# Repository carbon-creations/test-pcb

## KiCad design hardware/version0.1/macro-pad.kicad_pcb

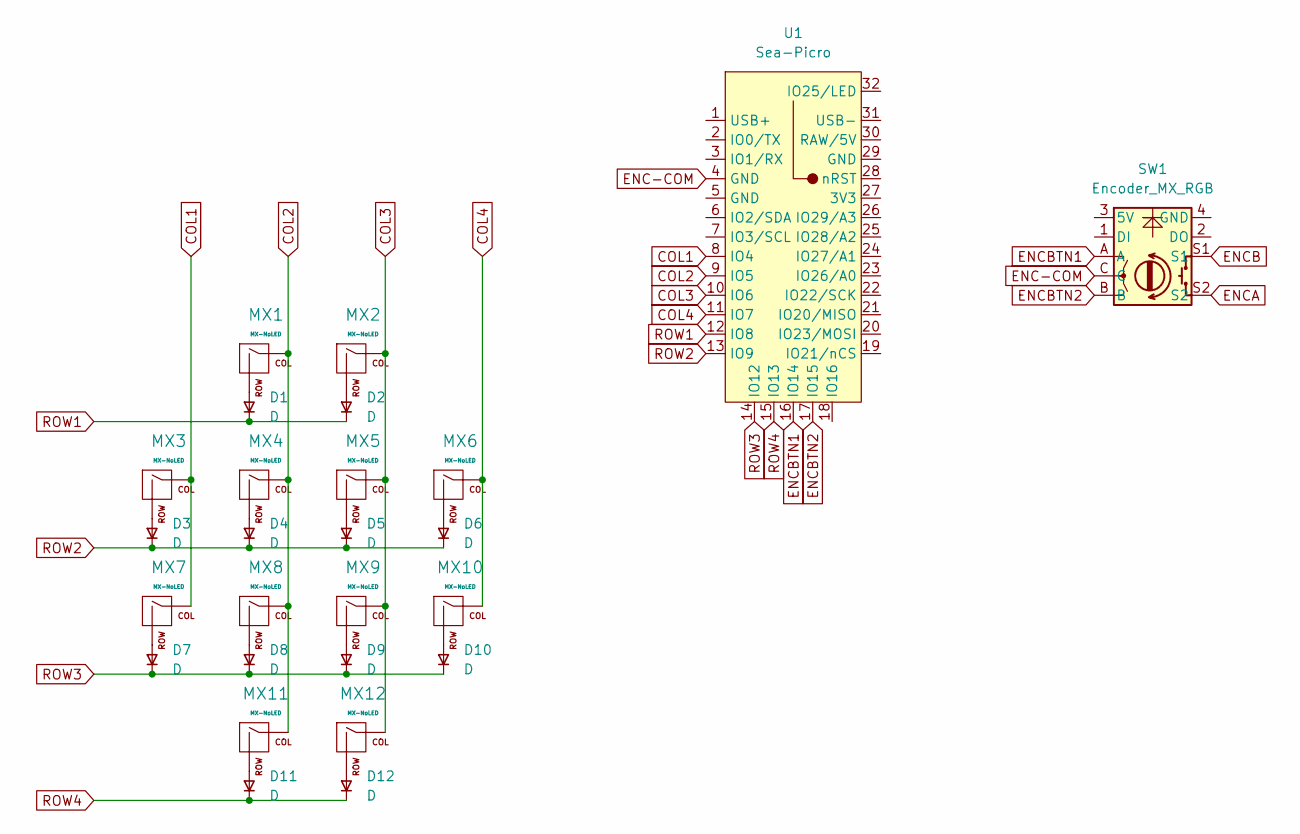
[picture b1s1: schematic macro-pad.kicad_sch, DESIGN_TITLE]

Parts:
D1, D2, D3, D4, D5, D6, D7, D8, D9, D10, D11, D12: D; D_SOD-123
MX1, MX2, MX3, MX4, MX5, MX6, MX7, MX8, MX9, MX10, MX11, MX12: MX-NoLED; Choc_Hotswap
SW1: Encoder_MX_RGB; RotaryEncoder_Alps_EC11E
U1: Sea-Picro; Sea-Picro_EXT_Module_Castellated

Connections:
COL1: MX3.1 (COL), MX7.1 (COL), U1.8 (IO4)
COL2: MX1.1 (COL), MX4.1 (COL), MX8.1 (COL), MX11.1 (COL), U1.9 (IO5)
COL3: MX2.1 (COL), MX5.1 (COL), MX9.1 (COL), MX12.1 (COL), U1.10 (IO6)
COL4: MX6.1 (COL), MX10.1 (COL), U1.11 (IO7)
ENC-COM: SW1.C, U1.4 (GND)
ENCA: SW1.S2
ENCB: SW1.S1
ENCBTN1: SW1.A, U1.16 (IO14)
ENCBTN2: SW1.B, U1.17 (IO15)
unnamed: D1.2 (A), MX1.2 (ROW)
unnamed: D2.2 (A), MX2.2 (ROW)
unnamed: D3.2 (A), MX3.2 (ROW)
unnamed: D4.2 (A), MX4.2 (ROW)
unnamed: D5.2 (A), MX5.2 (ROW)
unnamed: D6.2 (A), MX6.2 (ROW)
unnamed: D7.2 (A), MX7.2 (ROW)
unnamed: D8.2 (A), MX8.2 (ROW)
unnamed: D9.2 (A), MX9.2 (ROW)
unnamed: D10.2 (A), MX10.2 (ROW)
unnamed: D11.2 (A), MX11.2 (ROW)
unnamed: D12.2 (A), MX12.2 (ROW)
ROW1: D1.1 (K), D2.1 (K), U1.12 (IO8)
ROW2: D3.1 (K), D4.1 (K), D5.1 (K), D6.1 (K), U1.13 (IO9)
ROW3: D7.1 (K), D8.1 (K), D9.1 (K), D10.1 (K), U1.14 (IO12), U1.18 (IO16)
ROW4: D11.1 (K), D12.1 (K), U1.15 (IO13)

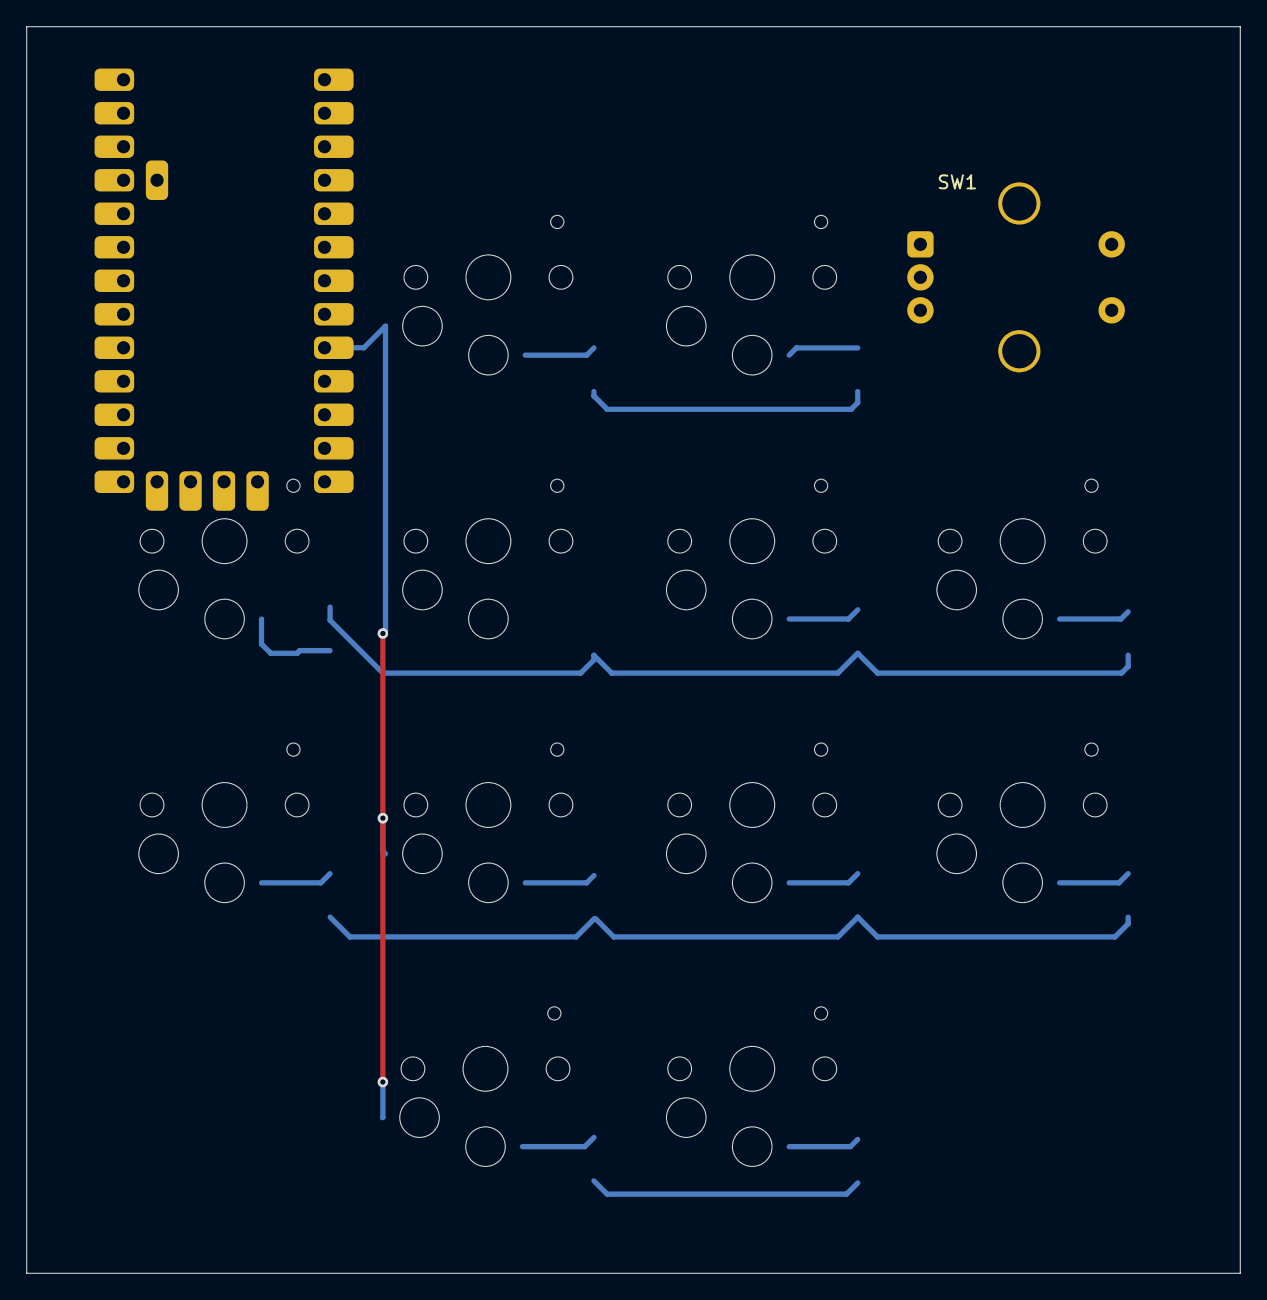
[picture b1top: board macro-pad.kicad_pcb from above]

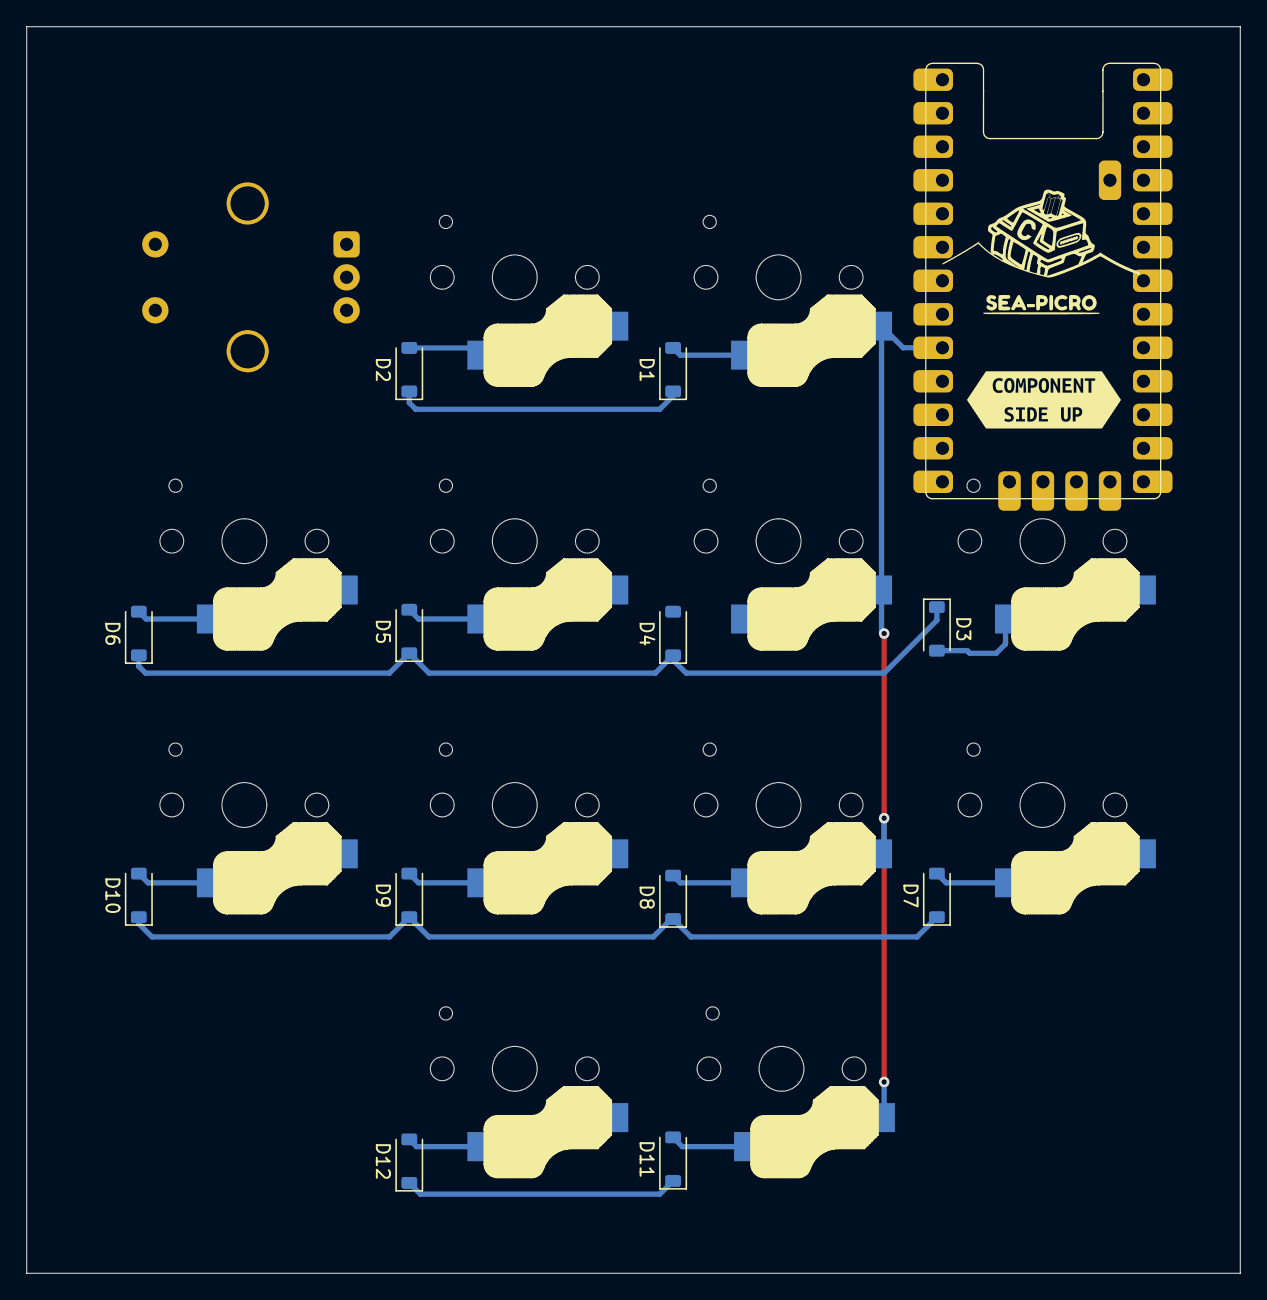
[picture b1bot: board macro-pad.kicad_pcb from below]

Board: 2 copper layers, 92.0 x 94.5 mm, 26 parts (13 on the bottom side), 23 nets.

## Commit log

2025-06-27 first comit
